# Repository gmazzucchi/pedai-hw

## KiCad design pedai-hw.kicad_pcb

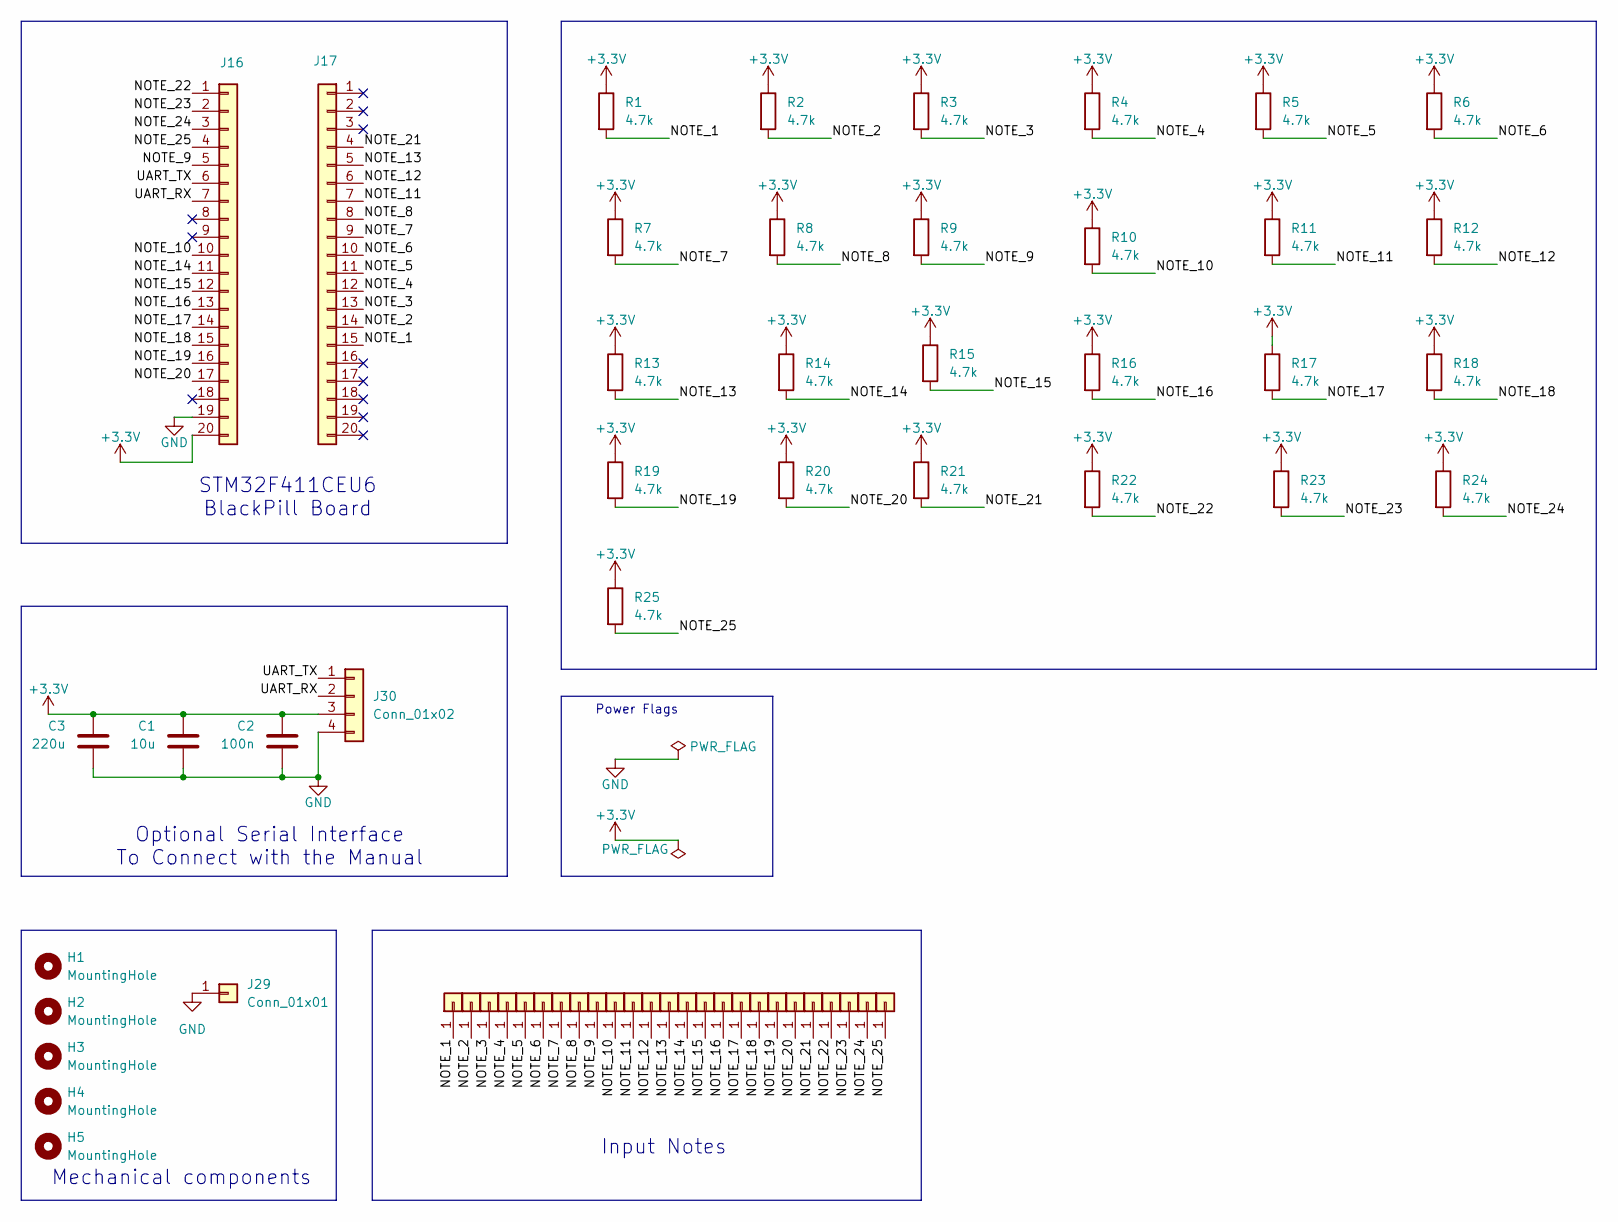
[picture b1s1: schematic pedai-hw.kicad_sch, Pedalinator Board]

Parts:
C1: 10u; C_0603_1608Metric
C2: 100n; C_0603_1608Metric
C3: 220u; C_0603_1608Metric
H1, H2, H3, H4, H5: MountingHole; MountingHole_3.2mm_M3_Pad
J2, J3, J4, J5, J6, J7, J8, J9, J10, J11, J12, J13, J14, J15, J18, J19, J20, J21, J22, J23, J24, J25, J26, J27, J28: Conn_01x01; PinHeader_1x01_P2.54mm_Vertical
J16: left_connector_blackpill; PinSocket_1x20_P2.54mm_Vertical
J17: right_connector_blackpill; PinSocket_1x20_P2.54mm_Vertical
J29: Conn_01x01; SolderWirePad_1x01_SMD_5x10mm
J30: Conn_01x02; PinHeader_1x04_P2.54mm_Vertical
R1, R2, R3, R4, R5, R6, R7, R8, R9, R10, R11, R12, R13, R14, R15, R16, R17, R18, R19, R20, R21, R22, R23, R24, R25: 4.7k; R_Axial_DIN0207_L6.3mm_D2.5mm_P10.16mm_Horizontal

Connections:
+3.3V: C1.1, C2.1, C3.1, J16.20, J30.3, R1.1, R2.1, R3.1, R4.1, R5.1, R6.1, R7.1, R8.1, R9.1, R10.1, R11.1, R12.1, R13.1, R14.1, R15.1, R16.1, R17.1, R18.1, R19.1, R20.1, R21.1, R22.1, R23.1, R24.1, R25.1
/NOTE_1: J2.1, J17.15, R1.2
/NOTE_2: J3.1, J17.14, R2.2
/NOTE_3: J4.1, J17.13, R3.2
/NOTE_4: J5.1, J17.12, R4.2
/NOTE_5: J6.1, J17.11, R5.2
/NOTE_6: J7.1, J17.10, R6.2
/NOTE_7: J8.1, J17.9, R7.2
/NOTE_8: J9.1, J17.8, R8.2
/NOTE_9: J10.1, J16.5, R9.2
/NOTE_10: J11.1, J16.10, R10.2
/NOTE_11: J12.1, J17.7, R11.2
/NOTE_12: J13.1, J17.6, R12.2
/NOTE_13: J14.1, J17.5, R13.2
/NOTE_14: J15.1, J16.11, R14.2
/NOTE_15: J16.12, J18.1, R15.2
/NOTE_16: J16.13, J19.1, R16.2
/NOTE_17: J16.14, J20.1, R17.2
/NOTE_18: J16.15, J21.1, R18.2
/NOTE_19: J16.16, J22.1, R19.2
/NOTE_20: J16.17, J23.1, R20.2
/NOTE_21: J17.4, J24.1, R21.2
/NOTE_22: J16.1, J25.1, R22.2
/NOTE_23: J16.2, J26.1, R23.2
/NOTE_24: J16.3, J27.1, R24.2
/NOTE_25: J16.4, J28.1, R25.2
/UART_RX: J16.7, J30.2
/UART_TX: J16.6, J30.1
GND: C1.2, C2.2, C3.2, J16.19, J29.1, J30.4

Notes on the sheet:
STM32F411CEU6 BlackPill Board
Optional Serial Interface To Connect with the Manual
Power Flags
Input Notes
Mechanical components

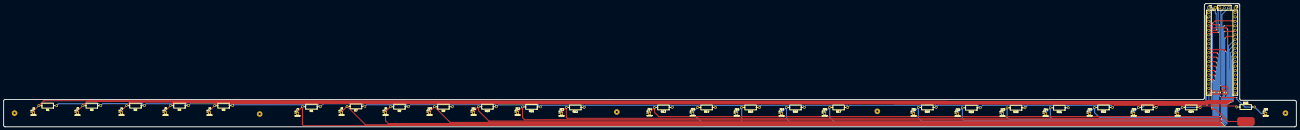
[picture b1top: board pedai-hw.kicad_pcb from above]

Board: 2 copper layers, 734.5 x 70.0 mm, 62 parts (0 on the bottom side), 29 nets.

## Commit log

2024-12-07 schematic first version, layout first draft
2024-12-16 fix: replaced 16 channel mux modules with 8 channels mux chips schematic concluded and added 3d models
2024-12-16 WIP: layout work in progress
2024-12-16 layout and routing finished
2024-12-16 fabrication output, silkscreen
2024-12-16 VERSION 0.9 ready for production silkscreen meme and not meme, ground pad, potentiometer for volume control and switch to turn off the device
2024-12-24 BREAKING: production
2025-08-20 feat: init project TODO: fix positions of the pads
2025-08-31 board is almost ready for production still looking for mistakes and inaccuracies
2025-09-03 fix: removed multiplexer and attached directly to GPIOs fix: removed I2S interface for sound feat: added a UART to communicate with the mainboard
2025-10-31 production
2025-10-31 added final fabrication zip
